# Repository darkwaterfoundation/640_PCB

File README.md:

640 DC Motor driver
=======================

#License 

Designed by Dark Water Technologies. Distributed under a Creative Commons Attribution, Share-Alike license.
Development kits based on this product should be distributed under a similar license.
Commercial products using the 640 boards as a reference design need not comply with this license; further questions can be sent to team@darkwater.io.
Check license.txt for more information.

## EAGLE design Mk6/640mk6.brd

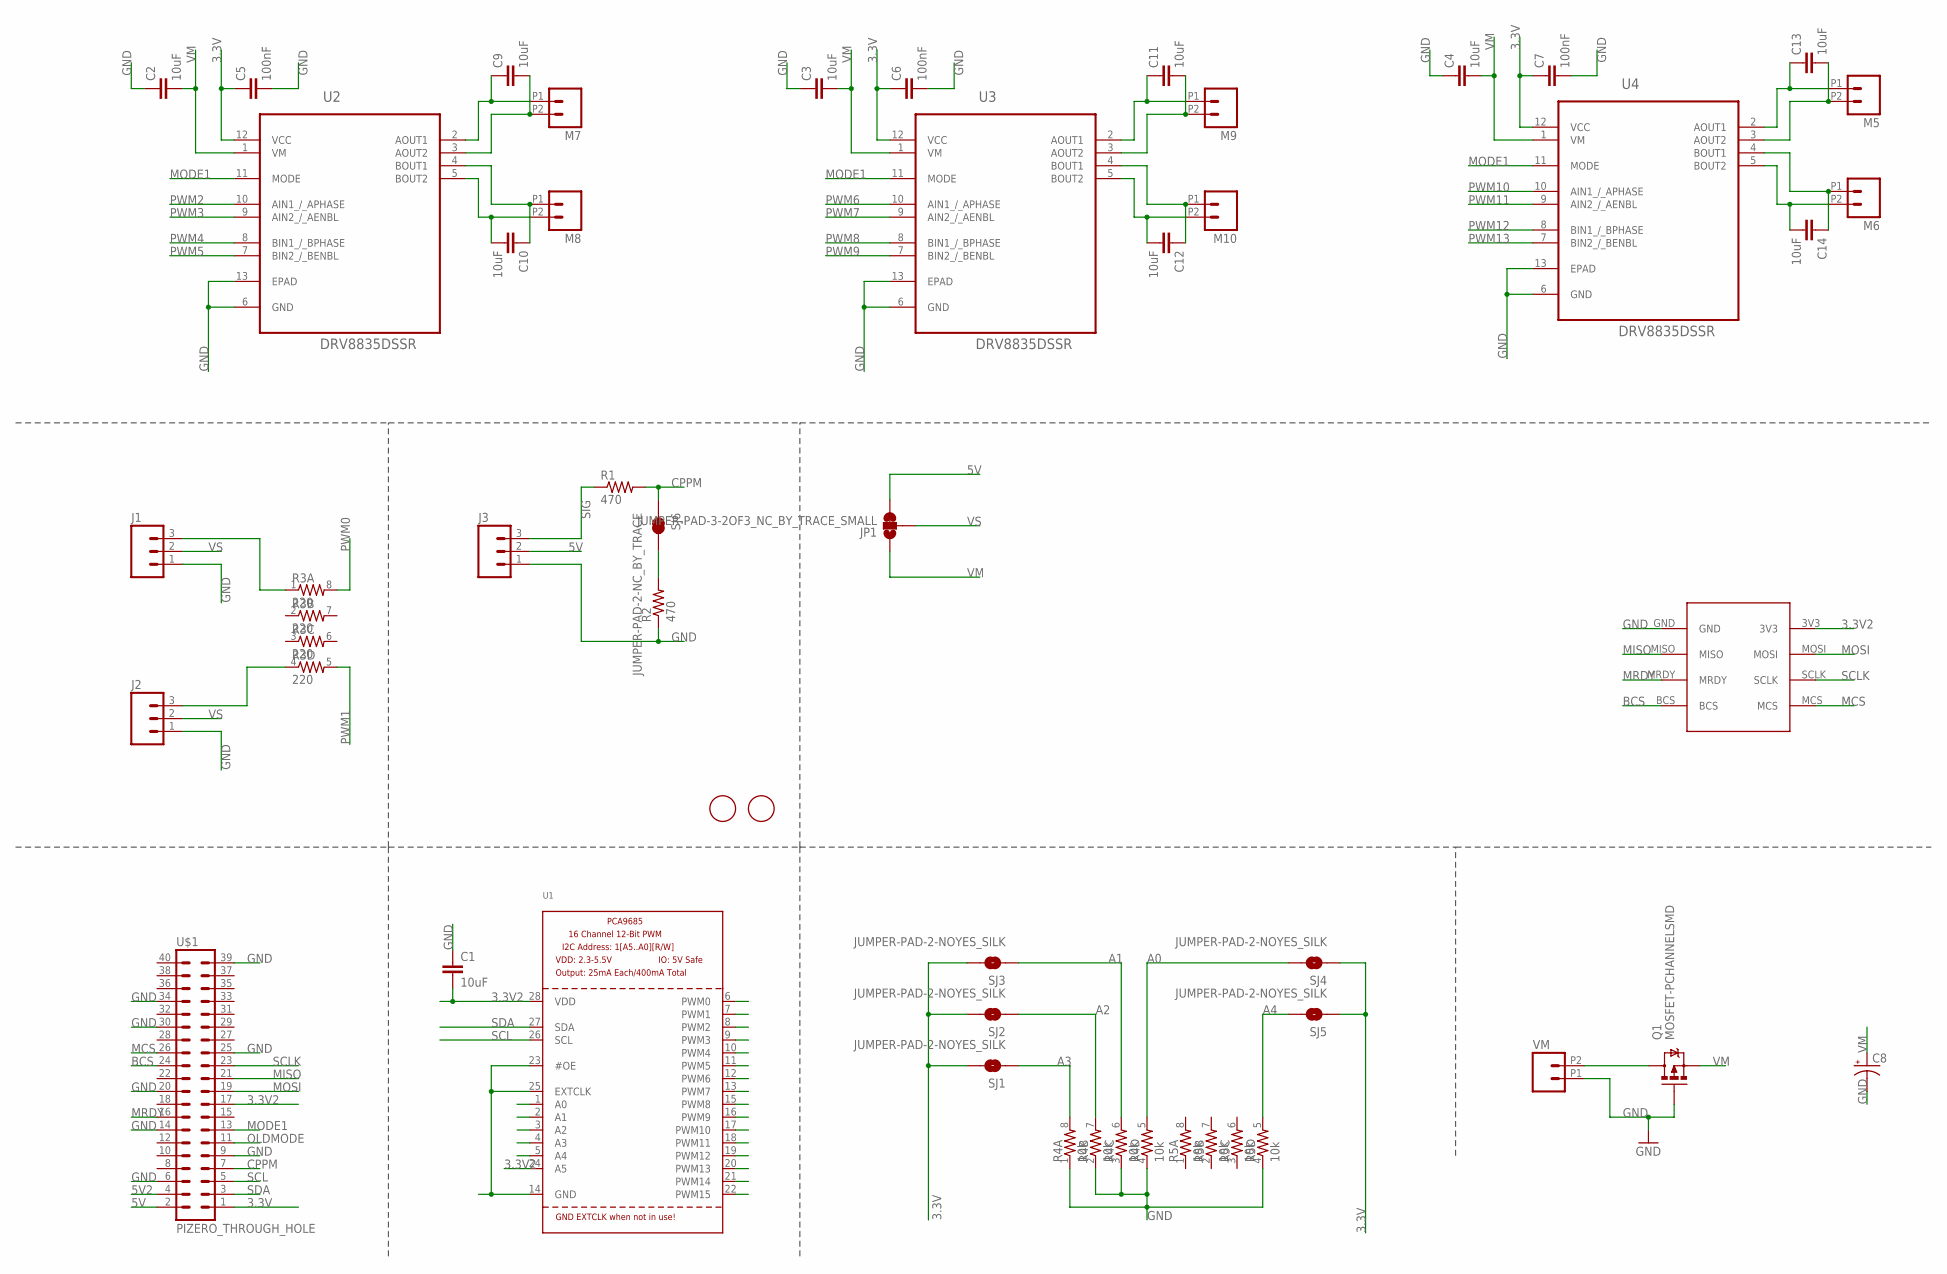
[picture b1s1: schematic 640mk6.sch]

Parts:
C1, C2, C3, C4, C9, C10, C11, C12, C13, C14: 10uF; 0805
C5, C6, C7: 100nF; 0805
C8: CAP_POLPTH1; CPOL-RADIAL-100UF-25V
FID1, FID2: FIDUCIAL; FIDUCIAL_1MM
J1, J2, J3: M03LOCK; 1X03_LOCK
JP1: JUMPER-PAD-3-2OF3_NC_BY_TRACE_SMALL; PAD-JUMPER-3-2OF3_NC_BY_TRACE_YES_SILK_FULL_BOX
M5, M6, M7, M8, M9, M10: M022.54MM_SCREWTERM; 1X02_2.54_SCREWTERM
Q1: MOSFET-PCHANNELSMD; SOT23-3
R1, R2: 470; 0805
R3: 220; 0603-ARV
R4, R5: 10k; 0603-ARV
SJ1, SJ2, SJ3, SJ4, SJ5: JUMPER-PAD-2-NOYES_SILK; PAD-JUMPER-2-NO_YES_SILK
SJ6: JUMPER-PAD-2-NC_BY_TRACE; PAD-JUMPER-2-NC_BY_TRACE_YES_SILK
U1: PCA9685; TSSOP28
U2, U3, U4: DRV8835DSSR; SON50P200X300X80-13N
U$1: PIZERO_THROUGH_HOLE; PIZERO_THOUGH_HOLE
U$2: 2X4PADS
VM: M022.54MM_SCREWTERM; 1X02_2.54_SCREWTERM

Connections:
3.3V: C5.1, C6.1, C7.1, SJ1.2, SJ2.2, SJ3.2, SJ4.1, SJ5.1, U2.12 (VCC), U3.12 (VCC), U4.12 (VCC), U$1.1
3.3V2: C1.2, U1.24 (A5), U1.28 (VDD), U$1.17, U$2.3V3
5V: J3.2, JP1.3, U$1.2
5V2: U$1.4
A0: R4.5 (2), SJ4.2, U1.1 (A0)
A1: R4.6 (2), SJ3.1, U1.2 (A1)
A2: R4.7 (2), SJ2.1, U1.3 (A2)
A3: R4.8 (2), SJ1.1, U1.4 (A3)
A4: R5.5 (2), SJ5.2, U1.5 (A4)
BCS: U$1.24, U$2.BCS
CPPM: R1.2, SJ6.1, U$1.7
GND: C1.1, C2.1, C3.1, C4.1, C5.2, C6.2, C7.2, C8.2 (-), J1.1, J2.1, J3.1, Q1.1 (G), R2.1, R4.1, R4.2 (1), R4.3 (1), R4.4 (1), R5.4 (1), U1.14 (GND), U1.23 (#OE), U1.25 (EXTCLK), U2.6 (GND), U2.13 (EPAD), U3.6 (GND), U3.13 (EPAD), U4.6 (GND), U4.13 (EPAD), U$1.6, U$1.9, U$1.14, U$1.20, U$1.25, U$1.30, U$1.34, U$1.39, U$2.GND, VM.P1 (1)
MCS: U$1.26, U$2.MCS
MISO: U$1.21, U$2.MISO
MODE1: U2.11 (MODE), U3.11 (MODE), U4.11 (MODE), U$1.13
MOSI: U$1.19, U$2.MOSI
MRDY: U$1.16, U$2.MRDY
unnamed: R2.2, SJ6.2
unnamed: J2.3, R3.4 (1)
unnamed: J1.3, R3.1
unnamed: Q1.3 (D), VM.P2 (2)
unnamed: C14.2, M6.P2 (2), U4.5 (BOUT2)
unnamed: C14.1, M6.P1 (1), U4.4 (BOUT1)
unnamed: C13.2, M5.P2 (2), U4.3 (AOUT2)
unnamed: C13.1, M5.P1 (1), U4.2 (AOUT1)
unnamed: C10.2, M8.P2 (2), U2.5 (BOUT2)
unnamed: C10.1, M8.P1 (1), U2.4 (BOUT1)
unnamed: C9.2, M7.P2 (2), U2.3 (AOUT2)
unnamed: C9.1, M7.P1 (1), U2.2 (AOUT1)
unnamed: C12.2, M10.P2 (2), U3.5 (BOUT2)
unnamed: C12.1, M10.P1 (1), U3.4 (BOUT1)
unnamed: C11.2, M9.P2 (2), U3.3 (AOUT2)
unnamed: C11.1, M9.P1 (1), U3.2 (AOUT1)
OLDMODE: U$1.11
PWM0: R3.8 (2), U1.6 (PWM0)
PWM1: R3.5 (2), U1.7 (PWM1)
PWM2: U1.8 (PWM2), U2.10 (AIN1_/_APHASE)
PWM3: U1.9 (PWM3), U2.9 (AIN2_/_AENBL)
PWM4: U1.10 (PWM4), U2.8 (BIN1_/_BPHASE)
PWM5: U1.11 (PWM5), U2.7 (BIN2_/_BENBL)
PWM6: U1.12 (PWM6), U3.10 (AIN1_/_APHASE)
PWM7: U1.13 (PWM7), U3.9 (AIN2_/_AENBL)
PWM8: U1.15 (PWM8), U3.8 (BIN1_/_BPHASE)
PWM9: U1.16 (PWM9), U3.7 (BIN2_/_BENBL)
PWM10: U1.17 (PWM10), U4.10 (AIN1_/_APHASE)
PWM11: U1.18 (PWM11), U4.9 (AIN2_/_AENBL)
PWM12: U1.19 (PWM12), U4.8 (BIN1_/_BPHASE)
PWM13: U1.20 (PWM13), U4.7 (BIN2_/_BENBL)
PWM14: U1.21 (PWM14)
PWM15: U1.22 (PWM15)
SCL: U1.26 (SCL), U$1.5
SCLK: U$1.23, U$2.SCLK
SDA: U1.27 (SDA), U$1.3
SIG: J3.3, R1.1
VM: C2.2, C3.2, C4.2, C8.1 (+), JP1.1, Q1.2 (S), U2.1 (VM), U3.1 (VM), U4.1 (VM)
VS: J1.2, J2.2, JP1.2

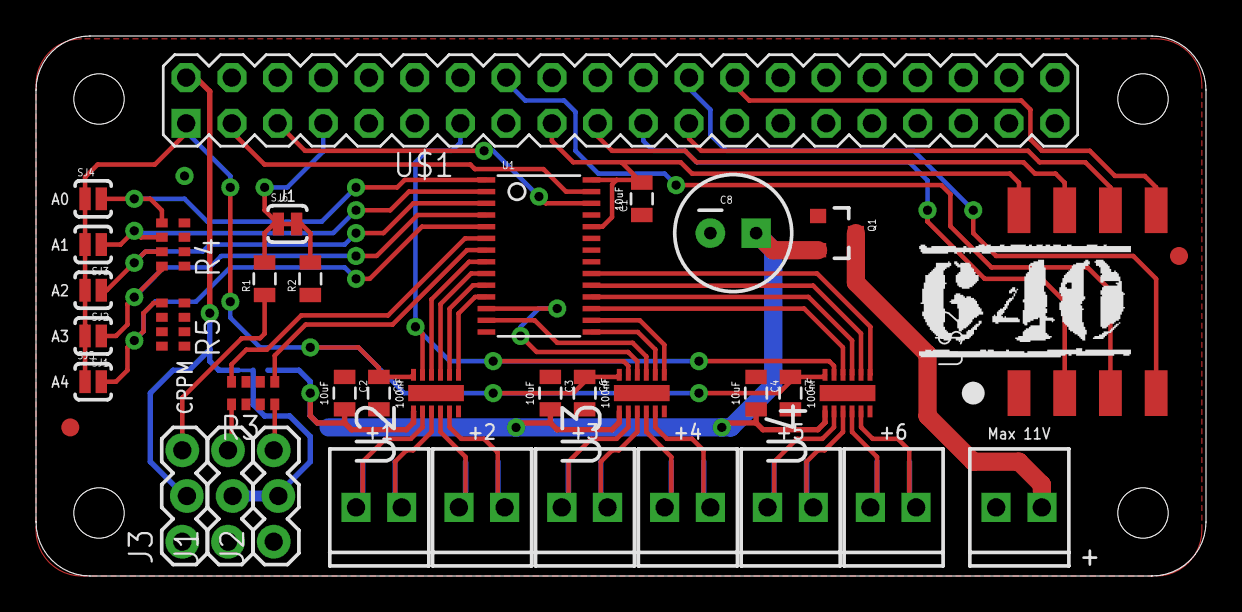
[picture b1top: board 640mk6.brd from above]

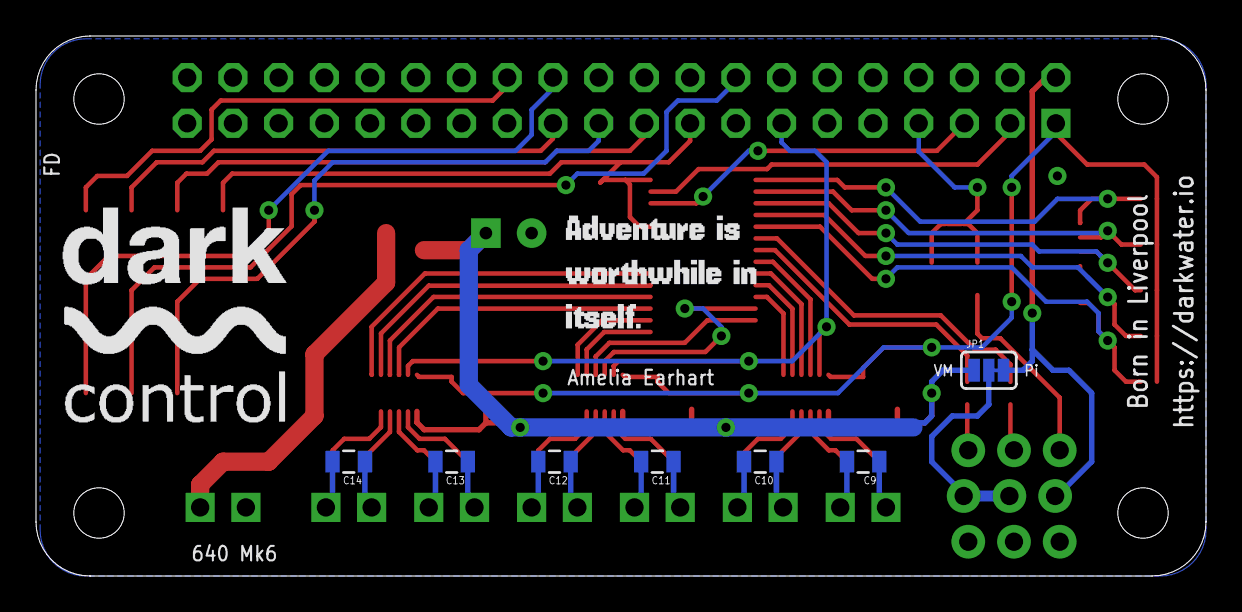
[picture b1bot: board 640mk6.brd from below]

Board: 2 copper layers, 65.0 x 30.0 mm, 48 parts (9 on the bottom side), 52 nets.

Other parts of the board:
U$3: DARKCONTROLSML
U$4: 640HORIZ
U$5: ADVENTURE

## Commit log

2016-08-13 Moved from other repository
2016-08-13 license
2016-08-13 added license.txt
2016-11-12 Added Mk6 designs

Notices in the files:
parts and their libraries:
SparkFun-Connectors: Licensing: Creative Commons ShareAlike 4.0 International - https://creativecommons.org/licenses/by-sa/4.0
